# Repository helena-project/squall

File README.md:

Squall
======

Squall is a low cost, 1 inch round BLE sensor tag based on the Nordic
nRF51822 BLE / Cortex M0 SoC. It is designed to be the basis for experimenting
with BLE tag platforms.

### Squall Versions

Squall comes in two flavors: a stripped down version with only the essentials
that has a raw cost just over $5. This includes the SoC, an antenna, expansion
headers, and a battery clip. This version is targeted towards sensor deployments
where a low cost per device is essential to permit larger deployments.

The second version adds USB support so that the nRF51822 can be programmed
with a serial bootloader, and adds a reset button and 32 kHz crystal. This
design is intended to be easier to get started with as it only requires
a USB connection to program. It also supports a rechargeable battery that
will charge over USB.

### Hardware Tools

To aid developing with Squall, there is a
[breakout board](/hardware/squall-breakout/rev_b) that makes it easier to debug
signals and program the board.

To program Squall over JTAG, there is an
[adapter board](https://github.com/lab11/nrf51-tools/tree/master/hardware/jlink_to_tag/rev_b)
that adapts the J-Link JTAG 20-pin header to the much smaller
[tag connect](http://www.tag-connect.com/catalog/6) header.

Daughter Boards
---------------

Squall is designed to be a base BLE platform with shields on top. A couple
shields have been developed:

- [Rain](/hardware/rain) - Sensing platform for wearable exploration.
- [BLEES](https://github.com/lab11/blees) - Environmental sensing platform.

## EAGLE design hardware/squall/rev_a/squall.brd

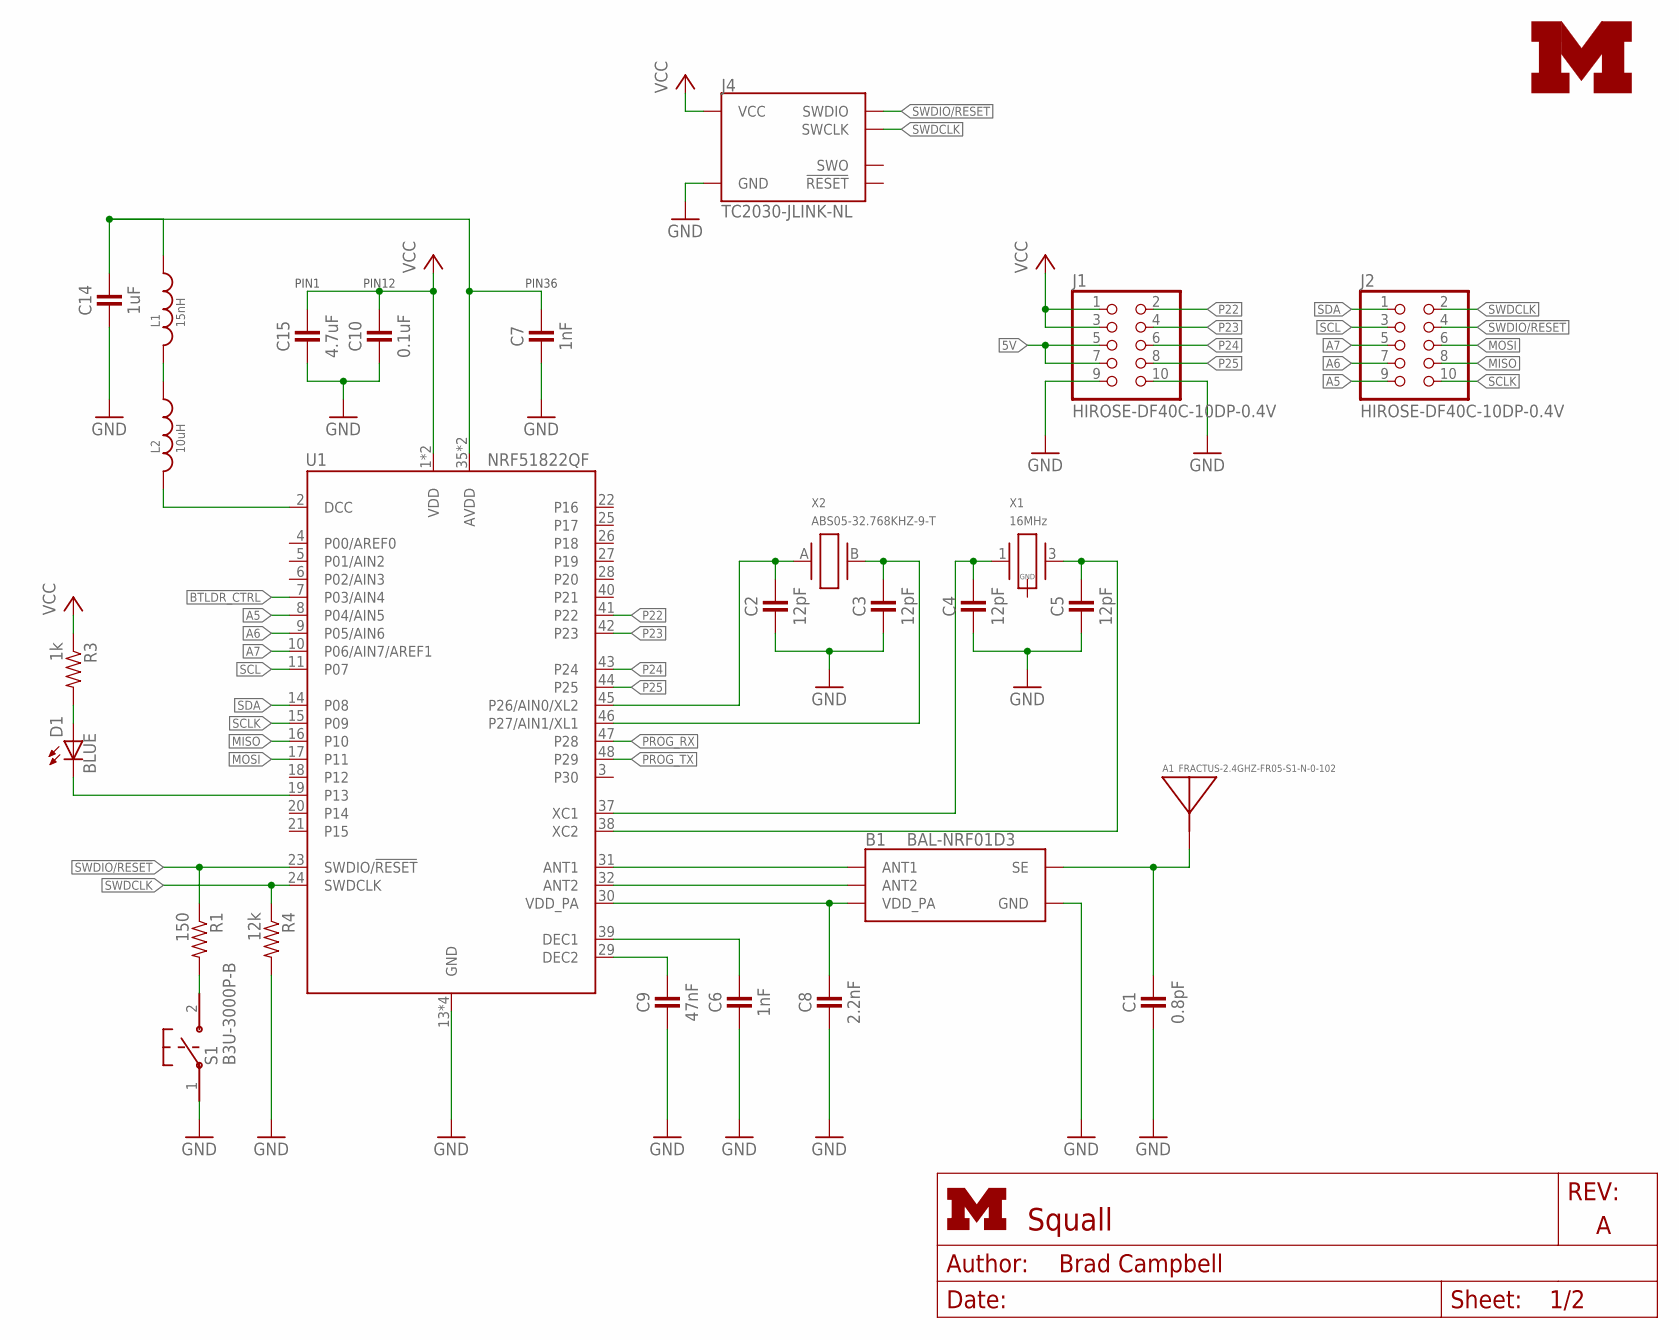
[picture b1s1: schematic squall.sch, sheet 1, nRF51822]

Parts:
A1: FRACTUS-2.4GHZ-FR05-S1-N-0-102; FRACTUS-ANTENNA-FR05-S1-N-0-102
B1: BAL-NRF01D3
C1: 0.8pF; 0402_CAP; MPN GRM1555C1HR80BA01D; DIGIKEY 490-6269-1-ND
C2, C3, C4, C5: 12pF; 0402_CAP; MPN GRM1555C1H120GA01D; DIGIKEY 490-6197-1-ND
C6, C7: 1nF; 0402_CAP; MPN GRM155R71H102KA01D; DIGIKEY 490-1303-1-ND
C8: 2.2nF; 0402_CAP; MPN GRM155R71E222KA01D; DIGIKEY 490-5419-1-ND
C9: 47nF; 0402_CAP; MPN C1005X7R1C473K050BC; DIGIKEY 445-1264-1-ND
C10: 0.1uF; 0402_CAP; MPN GRM155R61A104KA01D; DIGIKEY 490-1318-1-ND
C14: 1uF; 0402_CAP; MPN CL05B105KQ5NQNC; DIGIKEY 1276-1513-1-ND
C15: 4.7uF; 0402_CAP; MPN C1005X5R0J475K050BC; DIGIKEY 445-5947-1-ND
D1: BLUE; LED-0603
J1, J2: HIROSE-DF40C-10DP-0.4V; 2X5/SMD/0.4MM
J4: TC2030-JLINK-NL; TC2030-IDC-NL
L1: 15nH; 0402_CAP; MPN HK100515NJ-T; DIGIKEY 587-1521-1-ND
L2: 10uH; 0603_CAP; MPN LQM18FN100M00D; DIGIKEY 490-4025-1-ND
LOGO1: UMICH_SOLID_TINY; UMICH_SOLID_50MIL
R1: 150; 0402_RES; MPN MCR01MRTF1500; DIGIKEY RHM150CDCT-ND
R3: 1k; 0402_RES; MPN RC1005J102CS; DIGIKEY 1276-4376-1-ND
R4: 12k; 0402_RES; MPN RC1005F123CS; DIGIKEY 1276-4122-1-ND
S1: B3U-3000P-B
U1: NRF51822QF; QFN-48-6MM
X1: 16MHz; TXC-8Y; MPN 8Y-16.000MAAV-T; DIGIKEY 887-2003-1-ND
X2: ABS05-32.768KHZ-9-T; ABS05

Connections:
5V: J1.5, J1.7; also elsewhere on the board
A0: C2.1, U1.45 (P26/AIN0/XL2), X2.A (1)
A1: C3.1, U1.46 (P27/AIN1/XL1), X2.B (2)
A5: J2.9, U1.8 (P04/AIN5)
A6: J2.7, U1.9 (P05/AIN6)
A7: J2.5, U1.10 (P06/AIN7/AREF1)
AVDD: C7.1, C14.1, L1.1, U1.35 (AVDD), U1.36 (AVDD)
BTLDR_CTRL: U1.7 (P03/AIN4); also elsewhere on the board
DCC: L2.2, U1.2 (DCC)
GND: B1.GND, C1.2, C2.2, C3.2, C4.2, C5.2, C6.2, C7.2, C8.2, C9.2, C10.2, C14.2, C15.2, J1.9, J1.10, J4.5 (GND), R4.2, S1.1, U1.13 (GND), U1.33 (GND), U1.34 (GND), U1.GND; also elsewhere on the board
MISO: J2.8, U1.16 (P10)
MOSI: J2.6, U1.17 (P11)
unnamed: B1.ANT1, U1.31 (ANT1)
unnamed: B1.ANT2, U1.32 (ANT2)
unnamed: D1.C, U1.19 (P13)
unnamed: R1.2, S1.2
unnamed: A1.1, B1.SE, C1.1
unnamed: L1.2, L2.1
unnamed: C4.1, U1.37 (XC1), X1.1
unnamed: C5.1, U1.38 (XC2), X1.3 (2)
unnamed: C6.1, U1.39 (DEC1)
unnamed: C9.1, U1.29 (DEC2)
unnamed: D1.A, R3.2
P22: J1.2, U1.41 (P22)
P23: J1.4, U1.42 (P23)
P24: J1.6, U1.43 (P24)
P25: J1.8, U1.44 (P25)
PROG_RX: U1.47 (P28); also elsewhere on the board
PROG_TX: U1.48 (P29); also elsewhere on the board
SCL: J2.3, U1.11 (P07)
SCLK: J2.10, U1.15 (P09)
SDA: J2.1, U1.14 (P08)
SWDCLK: J2.2, J4.4 (SWCLK), R4.1, U1.24 (SWDCLK)
SWDIO/!RESET: J2.4, J4.2 (SWDIO), R1.1, U1.23 (SWDIO/!RESET)
VCC: C10.1, C15.1, J1.1, J1.3, J4.1 (VCC), R3.1, U1.1 (VDD), U1.12 (VDD); also elsewhere on the board
VDD_PA: B1.VCC (VDD_PA), C8.1, U1.30 (VDD_PA)

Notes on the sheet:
PIN1
PIN12
PIN36

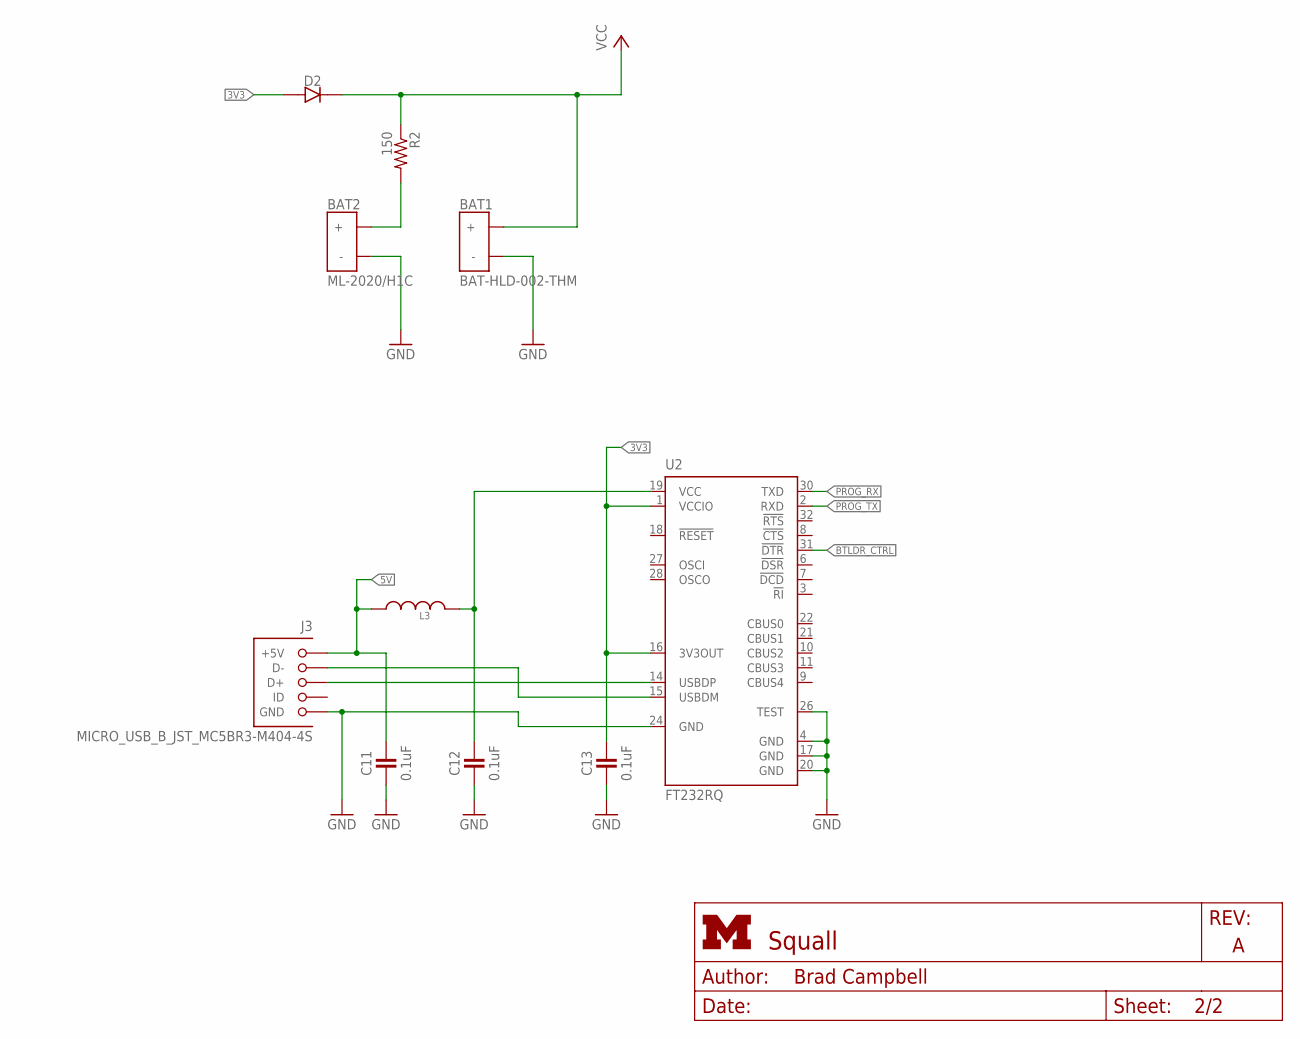
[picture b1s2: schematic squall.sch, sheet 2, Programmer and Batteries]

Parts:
BAT1: BAT-HLD-002-THM
BAT2: ML-2020/H1C
C11, C12, C13: 0.1uF; 0402_CAP; MPN GRM155R61A104KA01D; DIGIKEY 490-1318-1-ND
D2: DIODE; 0402_DIODE; MPN CDBQR0130L; DIGIKEY 641-1271-1-ND
J3: MICRO_USB_B_JST_MC5BR3-M404-4S; USB_MICRO_B-JST-MC5BR3-M404-4S-TB
L3: INDUCTOR0402; 0402_CAP; DIGIKEY 445-2979-1-ND
R2: 150; 0402_RES; MPN MCR01MRTF1500; DIGIKEY RHM150CDCT-ND
U2: FT232RQ; QFN32

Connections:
3V3: C13.1, D2.ANODE, U2.1 (VCCIO), U2.16 (3V3OUT)
5V: C11.1, J3.1 (+5V), L3.1; also elsewhere on the board
BTLDR_CTRL: U2.31 (!DTR); also elsewhere on the board
FTDI_VCC: C12.1, L3.2, U2.19 (VCC)
GND: BAT1.GND (-), BAT2.NEG (-), C11.2, C12.2, C13.2, J3.5 (GND), U2.4 (GND), U2.17 (GND), U2.20 (GND), U2.24 (GND), U2.26 (TEST); also elsewhere on the board
unnamed: BAT2.POS (+), R2.2
unnamed: J3.3 (D+), U2.14 (USBDP)
unnamed: J3.2 (D-), U2.15 (USBDM)
PROG_RX: U2.30 (TXD); also elsewhere on the board
PROG_TX: U2.2 (RXD); also elsewhere on the board
VCC: BAT1.POS1 (+), BAT1.POS2 (+), BAT1.POS3 (+), BAT1.POS4 (+), D2.CATHODE, R2.1; also elsewhere on the board

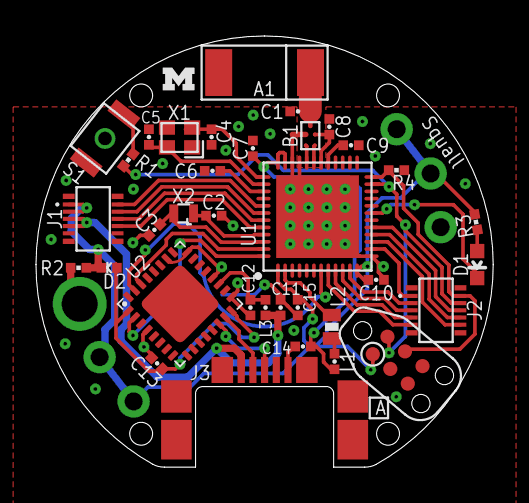
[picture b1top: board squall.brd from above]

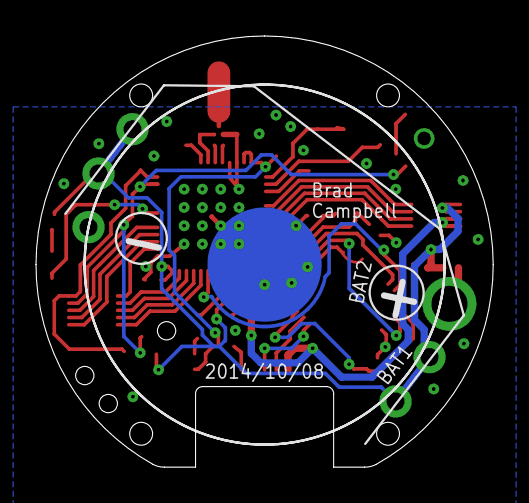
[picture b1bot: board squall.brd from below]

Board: 2 copper layers, 25.4 x 24.0 mm, 38 parts (2 on the bottom side), 41 nets.

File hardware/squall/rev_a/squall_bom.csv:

Qty,Value,Device,Package,Parts,Description,DIGIKEY,MOUSER,NEWARK,RICHARDSON_RFPD,Price Each (1000),Quantity (A),Cost (A),Quantity (B),Cost (B)
1,FRACTUS-2.4GHZ-FR05-S1-N-0-102,FRACTUS-2.4GHZ-FR05-S1-N-0-102,FRACTUS-ANTENNA-FR05-S1-N-0-102,A1,"Fractus Compact Reach XtendTM chip antenna is engineered specifically for Bluetooth,",,,,FR05-S1-N-0102B,0.74,1,0.74,1,0.74
1,BAL-NRF01D3,BAL-NRF01D3,BAL-NRF01D3,B1,"50 ohm nominal input / conjugate match balun to nRF51422-QFAA,",497-13637-1-ND,511-BAL-NRF01D3,,,0.337,1,0.337,1,0.337
1,BAT-HLD-002-THM,BAT-HLD-002-THM,BAT-HLD-002-THM,BAT1,RETAINER BATT CR2025/2032 PC PIN,BAT-HLD-001-THM-ND,,,,0.20125,1,0.20125,,0
1,ML-2020/H1C,ML-2020/H1C,ML-2020/H1C,BAT2,BATT LITH COIN 3V RECHARGE PINS 45mAh,P047-ND,658-ML-2020/H1CN,,,1.4025,,0,1,1.4025
1,0.8pF,CAPACITOR,0402_CAP,C1,0402 Capacitor,490-5419-1-ND,,,,0.0127,1,0.0127,1,0.0127
4,12pF,CAPACITOR,0402_CAP,"C2, C3, C4, C5",0402 Capacitor,490-6197-1-ND,,,,0.0178,2,0.0356,4,0.0712
2,1nF,CAPACITOR,0402_CAP,"C6, C7",0402 Capacitor,490-1303-1-ND,,,,0.01009,2,0.02018,2,0.02018
1,2.2nF,CAPACITOR,0402_CAP,C8,0402 Capacitor,490-5419-1-ND,,,,0.0127,1,0.0127,1,0.0127
1,47nF,CAPACITOR,0402_CAP,C9,0402 Capacitor,445-1264-1-ND,,,,0.0151,1,0.0151,1,0.0151
1,0.1uF,CAPACITOR,0402_CAP,C10,0402 Capacitor,445-4952-1-ND,,,,0.0136,1,0.0136,1,0.0136
3,0.1uF,CAPACITOR,0402_CAP,"C11, C12, C13",0402 Capacitor,490-1318-6-ND,,,,0.01,,0,3,0.03
1,1uF,CAPACITOR,0402_CAP,C14,0402 Capacitor,1276-1513-1-ND,,,,0.058,,0,1,0.058
1,4.7uF,CAPACITOR,0402_CAP,C15,0402 Capacitor,445-5947-1-ND,,,,0.122,,0,1,0.122
1,BLUE,LED0603,LED-0603,D1,LED 468NM BLUE CLEAR 0603 SMD,160-1647-1-ND,,,,0.0925,1,0.0925,1,0.0925
1,DIODE,DIODE,0402_DIODE,D2,DIODE SCHOTTKY 30V 0.1A 0402,641-1271-1-ND,750-CDBQR0130L,,,0.11,,0,1,0.11
2,HIROSE-DF40C-10DP-0.4V,HIROSE-DF40C-10DP-0.4V,2X5/SMD/0.4MM,"J1, J2",DF40 Series Header - 0.4MM Pitch,H11616CT-ND,798-DF40C10DP0.4V51,68X2585,,0.38815,2,0.7763,2,0.7763
1,MICRO_USB_B_JST_MC5BR3-M404-4S,MICRO_USB_B_JST_MC5BR3-M404-4S,USB_MICRO_B-JST-MC5BR3-M404-4S-TB,J3,Micro USB B mid mount,455-2567-2-ND,53X3655,,,0.60558,,0,1,0.60558
1,15nH,INDUCTOR0402,0402_CAP,L1,INDUCTOR HI FREQ 15NH 5% 0402,587-1521-1-ND,,,,0.034,1,0.034,1,0.034
1,10uH,INDUCTOR0603,0603_CAP,L2,INDUCTOR 10UH 50MA 0603,490-4025-1-ND,,,,0.07434,1,0.07434,1,0.07434
1,,INDUCTOR0402,0402_CAP,L3,FERRITE CHIP 30 OHM 1.7A 0402,445-2979-1-ND,,,,0.0334,,0,1,0.0334
2,150,RESISTOR,0402_RES,"R1, R2",Resistor,RHM150CDCT-ND,,,,0.00933,,0,2,0.01866
1,1k,RESISTOR,0402_RES,R3,Resistor,RHM1.0KCECT-ND,,,,0.00933,1,0.00933,1,0.00933
1,12k,RESISTOR,0402_RES,R4,Resistor,RHM12.0KCDCT-ND,,,,0.00933,1,0.00933,1,0.00933
1,B3U-3000P-B,B3U-3000P-B,B3U-3000P-B,S1,SWITCH TACTILE SPST-NO 0.05A 12V,SW1256CT-ND,,,,0.66414,,0,1,0.66414
1,NRF51822QF,NRF51822QF,QFN-48-6MM,U1,Multiprotocol Bluetooth® 4.0 low energy/2.4 GHz RF SoC 256K,1490-1031-1-ND,,,,2.31,1,2.31,1,2.31
1,FT232RQ,FT232RQ,QFN32,U2,IC USB FS SERIAL UART 32-QFN,768-1008-1-ND,,91K9919,,3.301,,0,1,3.301
1,16MHz,TXC-8Y,TXC-8Y,X1,CRYSTAL 16MHZ 8PF SMD,887-2003-1-ND,,,,0.782,1,0.782,1,0.782
1,ABS05-32.768KHZ-9-T,ABS05-32.768KHZ-9-T,ABS05,X2,32.768kHz Crystal,535-11897-1-ND,,,,1.061,,0,1,1.061
,,,,,BATTERY LITHIUM COIN 3V 20MM CR2032,P189-ND,,,,0.15579,1,0.15579,,
,,,,,,,,,,,,5.63172,,12.71656

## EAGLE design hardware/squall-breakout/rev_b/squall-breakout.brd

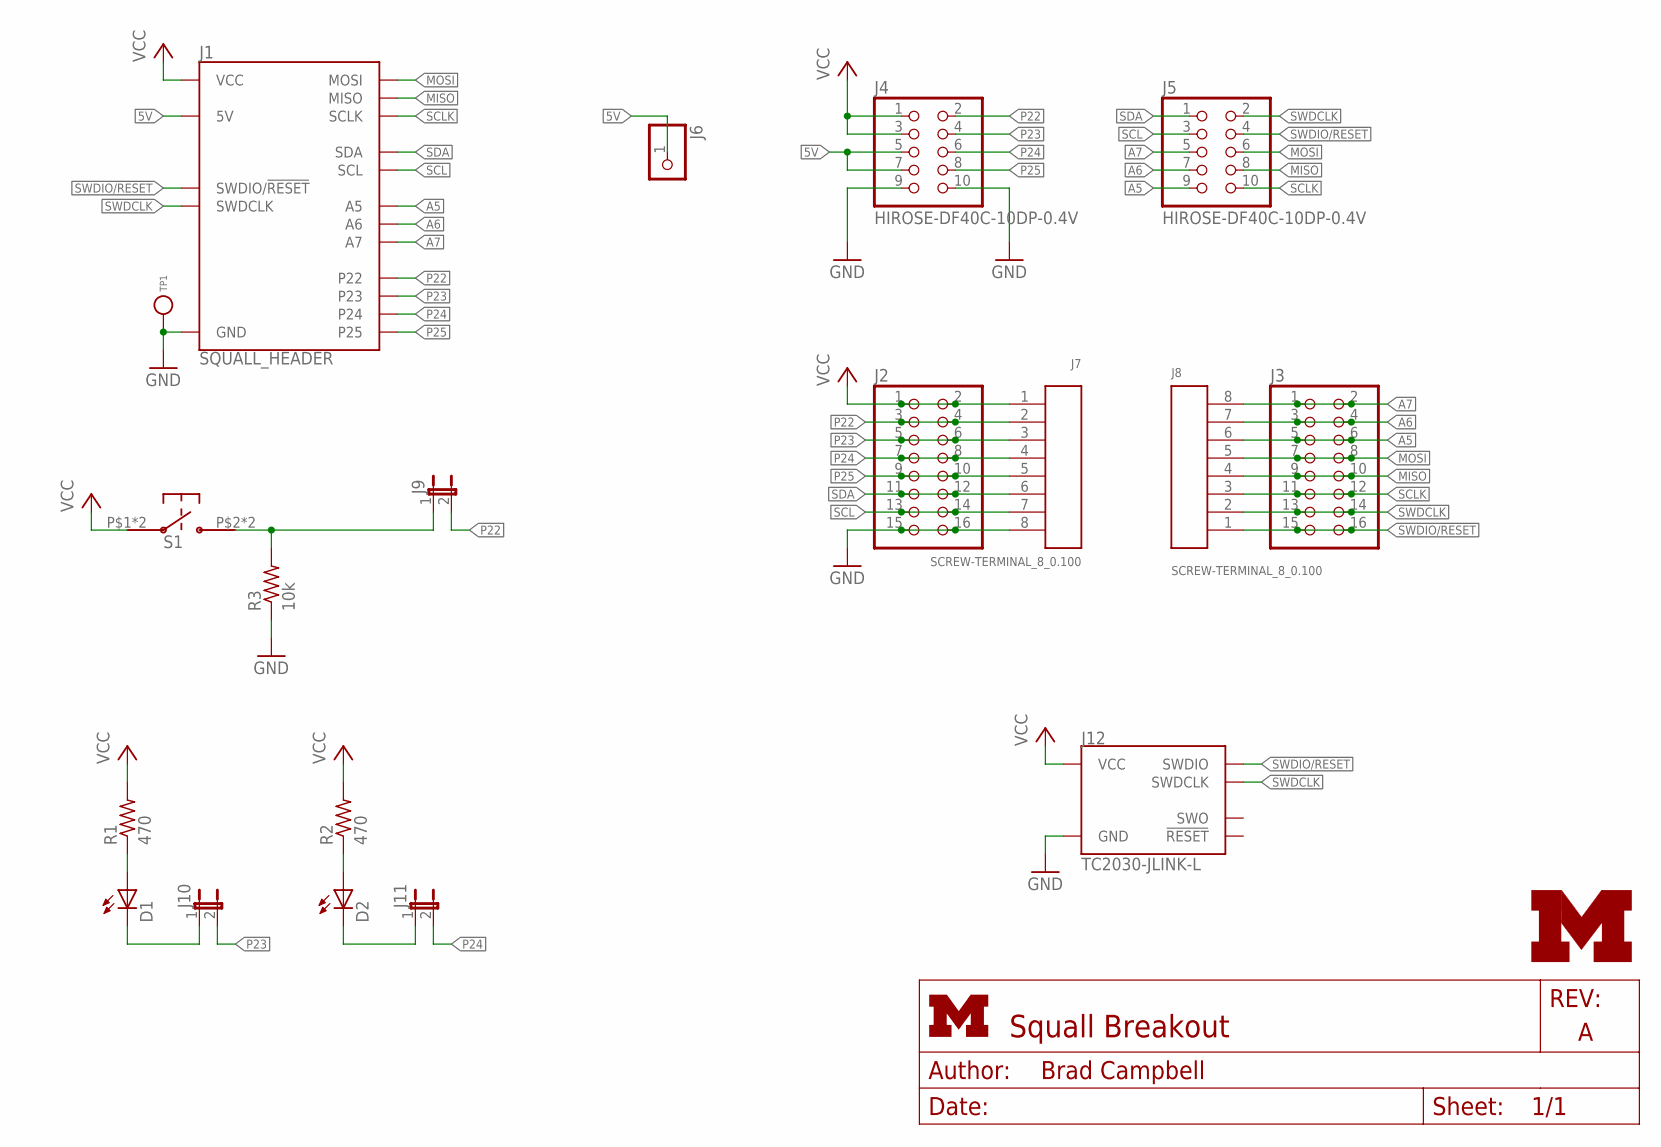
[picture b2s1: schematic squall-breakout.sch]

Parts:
D1, D2: LED0603; LED-0603
J1: SQUALL_HEADER
J2, J3: PINHD-2X8; 2X08
J4, J5: HIROSE-DF40C-10DP-0.4V; 2X5/SMD/0.4MM
J6: PINHD-1X1; 1X01
J7, J8: SCREW-TERMINAL_8_0.100; CONN_BLOCK_8
J9, J10, J11: JUMPER-2PTH; 1X02
J12: TC2030-JLINK-L; TC2030-IDC
LOGO1: UMICH_SOLID_TINY; UMICH_SOLID_50MIL
R1, R2: 470; R0603
R3: 10k; R0603
S1: EVQP2
TP1: TEST_POINT_0.112IN; TESTPOINT_0.112IN

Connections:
5V: J1.A5 (5V), J1.A7 (5V), J4.5, J4.7, J6.1
A5: J1.B9 (A5), J3.5, J3.6, J5.9, J8.6
A6: J1.B7 (A6), J3.3, J3.4, J5.7, J8.7
A7: J1.B5 (A7), J3.1, J3.2, J5.5, J8.8
GND: J1.A9 (GND), J1.A10 (GND), J2.15, J2.16, J4.9, J4.10, J7.8, J12.5 (GND), R3.1, TP1.1
MISO: J1.B8 (MISO), J3.9, J3.10, J5.8, J8.4
MOSI: J1.B6 (MOSI), J3.7, J3.8, J5.6, J8.5
unnamed: J9.1, R3.2, S1.P$2, S1.P$4
unnamed: D1.A, R1.1
unnamed: D1.C, J10.1
unnamed: D2.A, R2.1
unnamed: D2.C, J11.1
P22: J1.A2 (P22), J2.3, J2.4, J4.2, J7.2, J9.2
P23: J1.A4 (P23), J2.5, J2.6, J4.4, J7.3, J10.2
P24: J1.A6 (P24), J2.7, J2.8, J4.6, J7.4, J11.2
P25: J1.A8 (P25), J2.9, J2.10, J4.8, J7.5
SCL: J1.B3 (SCL), J2.13, J2.14, J5.3, J7.7
SCLK: J1.B10 (SCLK), J3.11, J3.12, J5.10, J8.3
SDA: J1.B1 (SDA), J2.11, J2.12, J5.1, J7.6
SWDCLK: J1.B2 (SWDCLK), J3.13, J3.14, J5.2, J8.2, J12.4 (SWDCLK)
SWDIO/!RESET: J1.B4 (SWDIO/!RESET), J3.15, J3.16, J5.4, J8.1, J12.2 (SWDIO)
VCC: J1.A1 (VCC), J1.A3 (VCC), J2.1, J2.2, J4.1, J4.3, J7.1, J12.1 (VCC), R1.2, R2.2, S1.P$1, S1.P$3

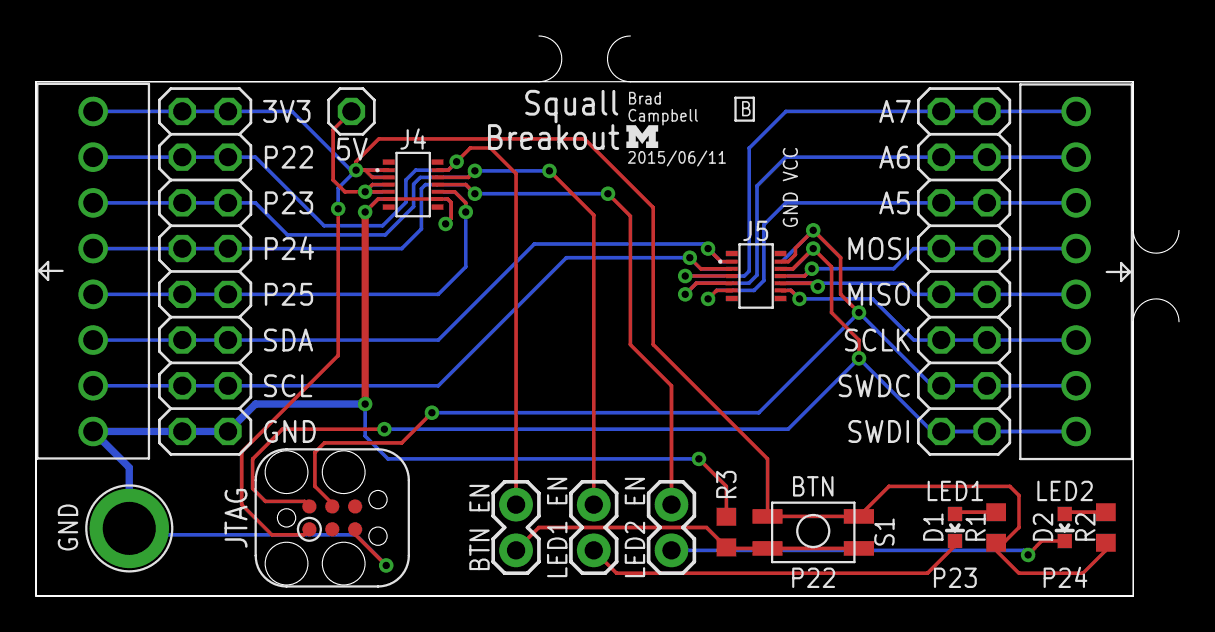
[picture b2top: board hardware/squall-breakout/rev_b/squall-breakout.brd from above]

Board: 2 copper layers, 63.5 x 31.1 mm, 20 parts (0 on the bottom side), 22 nets.

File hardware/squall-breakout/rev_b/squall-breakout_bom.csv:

# Bill of Materials
# Converted from squall-breakout_bom.xlsx
# Generated by bom_to_text.py

Qty,Value,Device,Package,Parts,Description,DIGIKEY,MOUSER,NEWARK
2,,LED0603,LED-0603,"D1, D2",LEDs,,,
2,SQUALL_HEADER,SQUALL_HEADER,SQUALL_HEADER,J1,Header for a sensor board on top of the Squall BLE tag board.,H11617CT-ND,,
2,,PINHD-2X8,2X08,"J2, J3",PIN HEADER,609-3364-ND,649-68602-116HLF,20M2833
2,HIROSE-DF40C-10DP-0.4V,HIROSE-DF40C-10DP-0.4V,2X5/SMD/0.4MM,"J4, J5",DF40 Series Header - 0.4MM Pitch,H11616CT-ND,798-DF40C10DP0.4V51,68X2585
1,,PINHD-1X1,1X01,J6,PIN HEADER,A107006-ND,,
2,SCREW-TERMINAL_8_0.100,SCREW-TERMINAL_8_0.100,CONN_BLOCK_8,"J7, J8",8x 0.100 in screw terminal block,277-1279-ND,651-1725711,71C4111
3,,JUMPER-2PTH,1X02,"J9, J10, J11",Jumper,3M9447-ND,,
2,470,R-US_R0603,R0603,"R1, R2","RESISTOR, American symbol",,,
1,10k,R-US_R0603,R0603,R3,"RESISTOR, American symbol",,,
1,EVQP2,EVQP2,EVQP2,S1,SWITCH TACTILE SPST-NO 0.02A 15V,P11084SCT-ND,,
1,TEST_POINT_0.112IN,TEST_POINT_0.112IN,TESTPOINT_0.112IN,TP1,"Solder terminal, turreted",,,40F6015

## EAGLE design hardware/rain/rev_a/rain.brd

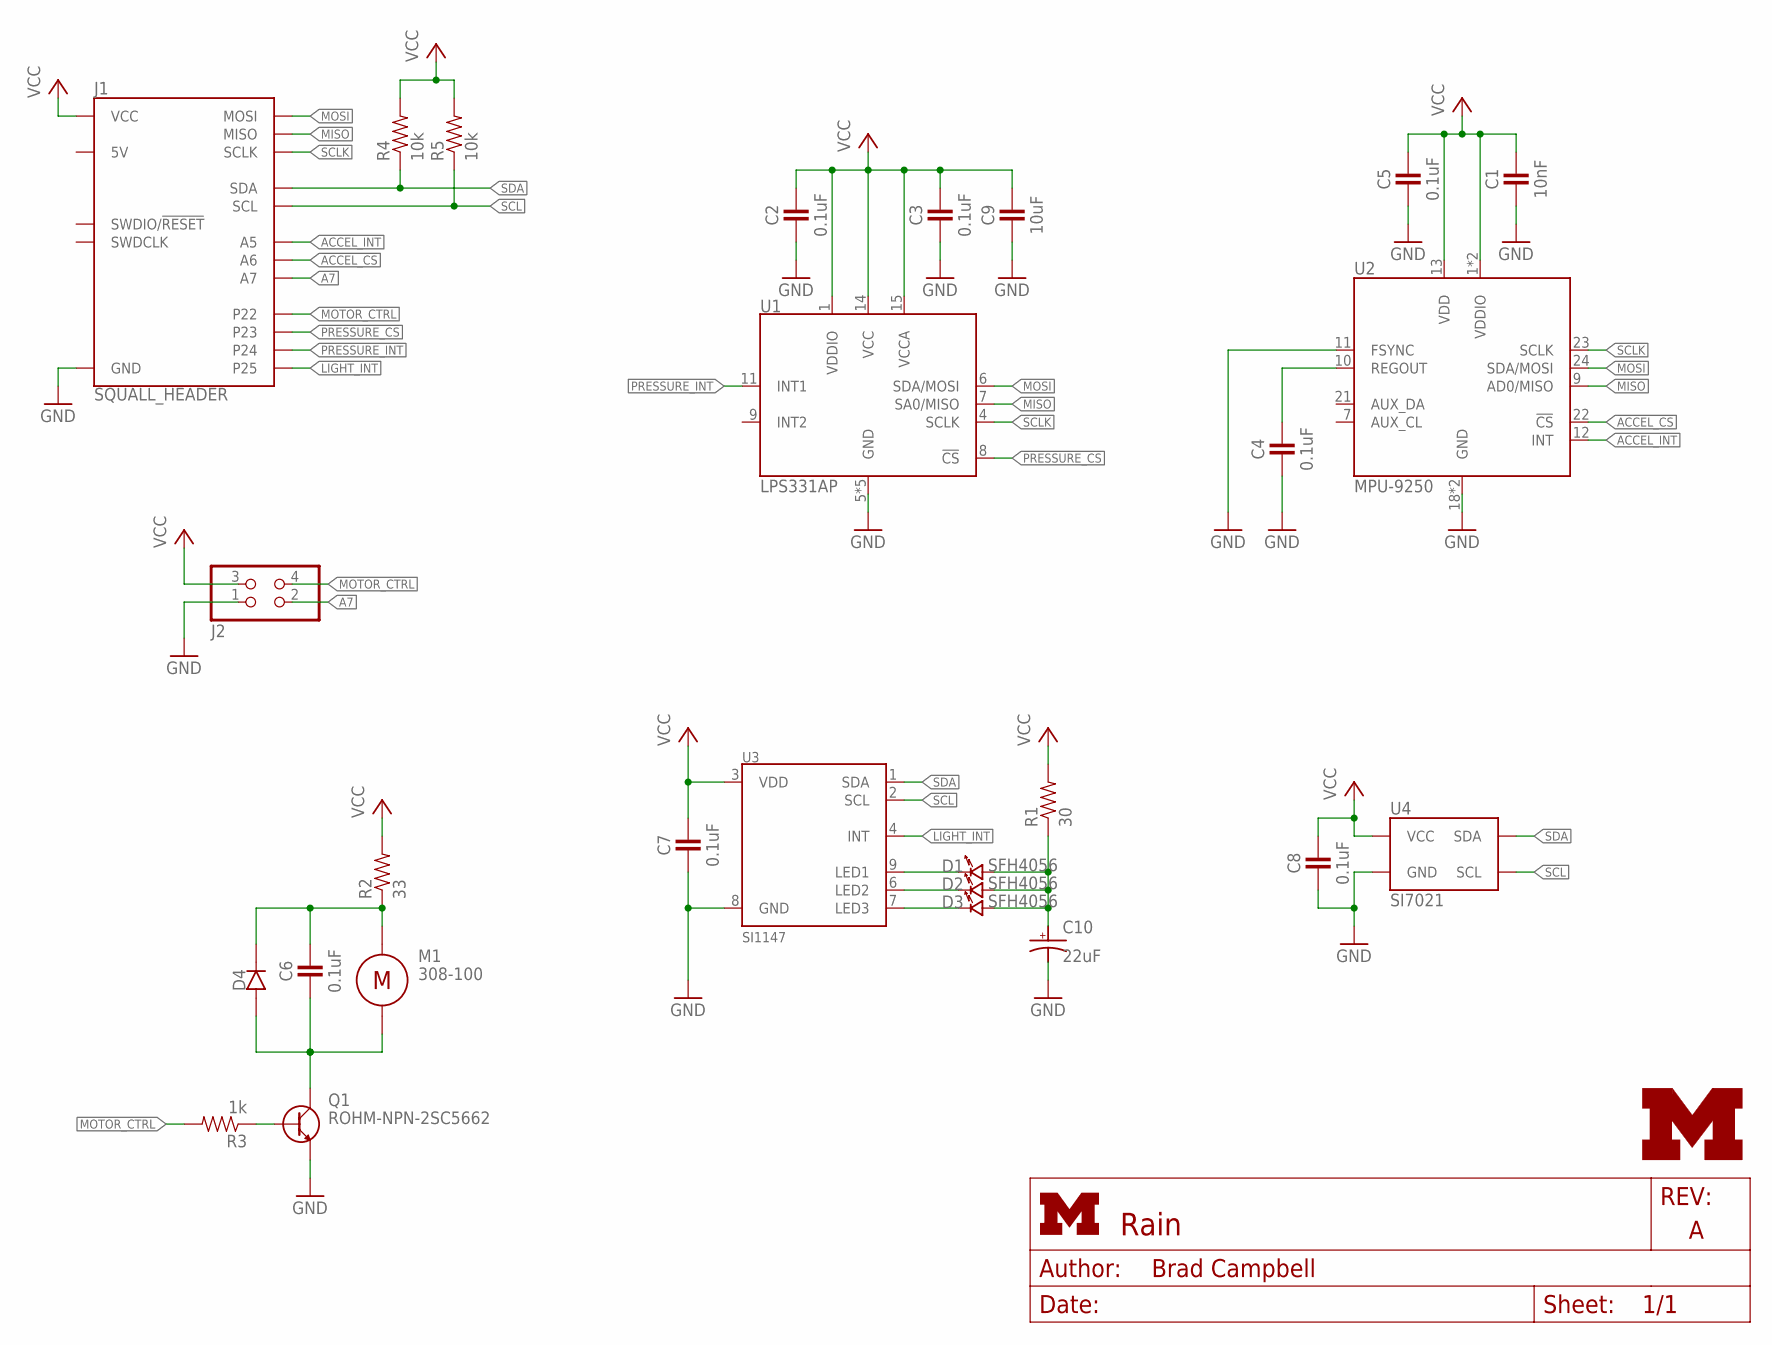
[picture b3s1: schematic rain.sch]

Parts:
C1: 10nF; 0402_CAP; DIGIKEY 490-1312-1-ND
C2, C3, C4, C5, C6, C7, C8: 0.1uF; 0402_CAP; DIGIKEY 490-1318-1-ND
C9: 10uF; 0402_CAP; DIGIKEY 445-8919-1-ND
C10: 22uF; CAP0603; DIGIKEY 511-1493-1-ND
D1, D2, D3: SFH4056
D4: DIODE; 0402_DIODE; DIGIKEY 641-1277-1-nd
J1: SQUALL_HEADER
J2: PINHD-2X2; 2X02; DIGIKEY 609-3201-ND
LOGO1: UMICH_SOLID_TINY; UMICH_SOLID_50MIL
M1: 308-100
Q1: ROHM-NPN-2SC5662; VMT3
R1: 30; 0402_RES; DIGIKEY RHM30CECT-ND
R2: 33; 0402_RES; DIGIKEY RHM33CECT-ND
R3: 1k; 0402_RES; DIGIKEY RHM1.0KCECT-ND
R4, R5: 10k; 0402_RES; DIGIKEY RHM10.0KCDCT-ND
U1: LPS331AP; HCLGA-16/3MM
U2: MPU-9250; QFN-24/3MM
U3: SI1147; QFN-10/2MM
U4: SI7021; DFN-6/3MM

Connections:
!ACCEL_CS: J1.B7 (A6), U2.22 (!CS)
!PRESSURE_CS: J1.A4 (P23), U1.8 (!CS)
A7: J1.B5 (A7), J2.2
ACCEL_INT: J1.B9 (A5), U2.12 (INT)
GND: C1.2, C2.2, C3.2, C4.2, C5.2, C7.2, C8.2, C9.2, C10.NEG (ANODE), J1.A9 (GND), J1.A10 (GND), J2.1, Q1.2 (EMITTER), U1.5 (GND), U1.10 (GND), U1.12 (GND), U1.13 (GND), U1.16 (GND), U2.11 (FSYNC), U2.18 (GND), U2.20 (GND), U3.8 (GND), U4.2 (GND)
LIGHT_INT: J1.A8 (P25), U3.4 (INT)
MISO: J1.B8 (MISO), U1.7 (SA0/MISO), U2.9 (AD0/MISO)
MOSI: J1.B6 (MOSI), U1.6 (SDA/MOSI), U2.24 (SDA/MOSI)
MOTOR_CTRL: J1.A2 (P22), J2.4, R3.2
unnamed: C6.1, D4.CATHODE, M1.POS, R2.1
unnamed: C6.2, D4.ANODE, M1.NEG, Q1.3 (COLLECTOR)
unnamed: C4.1, U2.10 (REGOUT)
unnamed: D1.CATHODE, U3.9 (LED1)
unnamed: Q1.1 (BASE), R3.1
unnamed: D2.CATHODE, U3.6 (LED2)
unnamed: D3.CATHODE, U3.7 (LED3)
unnamed: C10.POS (CATHODE), D1.ANODE, D2.ANODE, D3.ANODE, R1.1
PRESSURE_INT: J1.A6 (P24), U1.11 (INT1)
SCL: J1.B3 (SCL), R5.1, U3.2 (SCL), U4.6 (SCL)
SCLK: J1.B10 (SCLK), U1.4 (SCLK), U2.23 (SCLK)
SDA: J1.B1 (SDA), R4.1, U3.1 (SDA), U4.1 (SDA)
VCC: C1.1, C2.1, C3.1, C5.1, C7.1, C8.1, C9.1, J1.A1 (VCC), J1.A3 (VCC), J2.3, R1.2, R2.2, R4.2, R5.2, U1.1 (VDDIO), U1.14 (VCC), U1.15 (VCCA), U2.1 (VDDIO), U2.8 (VDDIO), U2.13 (VDD), U3.3 (VDD), U4.5 (VCC)

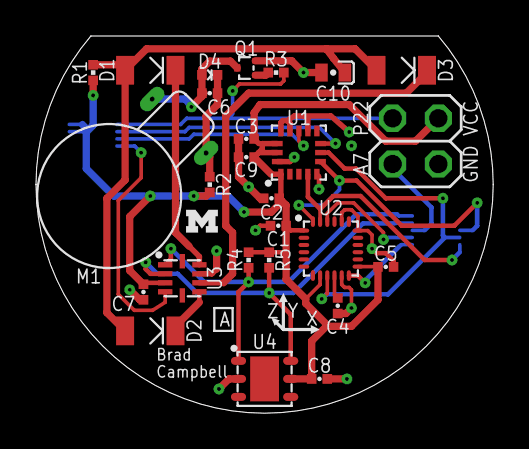
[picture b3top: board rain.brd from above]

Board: 2 copper layers, 25.4 x 21.0 mm, 28 parts (0 on the bottom side), 22 nets.

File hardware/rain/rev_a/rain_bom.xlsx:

Qty | Value | Device | Package | Parts | Description | DIGIKEY | PRECISION_MICRODRIVES
1 | 10nF | CAPACITOR | 0402_CAP | C1 | 0402 Capacitor | 490-1312-1-ND
7 | 0.1uF | CAPACITOR | 0402_CAP | C2, C3, C4, C5, C6, C7, C8 | 0402 Capacitor | 490-1318-1-ND
1 | 10uF | CAPACITOR | 0402_CAP | C9 | 0402 Capacitor | 445-8919-1-ND
1 | 22uF | CAP_POL0603 | CAP0603 | C10 | 0603 Tantalum Capacitor | 511-1493-1-ND
3 | SFH4056 | SFH4056 | SFH4056 | D1, D2, D3 | LED IR EMITTER 850NM | 475-3042-1-ND
1 | DIODE | DIODE | 0402_DIODE | D4 |  | 641-1277-1-ND
2 | SQUALL_HEADER | SQUALL_HEADER | SQUALL_HEADER | J1 | Header for a sensor board on top of the Squall BLE tag board. | H11617CT-ND
1 |  | PINHD-2X2 | 2X02 | J2 | PIN HEADER | 609-3201-ND
1 | 308-100 | 308-100 | 308-100 | M1 | Pico Vibe |  | 308-100
1 | ROHM-NPN-2SC5662 | ROHM-NPN-2SC5662 | VMT3 | Q1 |  | 2SC5662T2LPCT-ND
1 | 30 | RESISTOR0402_RES | 0402_RES | R1 | Resistor | RHM30CECT-ND
1 | 33 | RESISTOR0402_RES | 0402_RES | R2 | Resistor | RHM33CECT-ND
1 | 1k | RESISTOR0402_RES | 0402_RES | R3 | Resistor | RHM1.0KCECT-ND
2 | 10k | RESISTOR0402_RES | 0402_RES | R4, R5 | Resistor | RHM10.0KCDCT-ND
1 | LPS331AP | LPS331AP | HCLGA-16/3MM | U1 | IC PRESSURE SENSOR PIEZO 16HCLGA | 497-12927-1-ND
1 | MPU-9250 | MPU-9250 | QFN-24/3MM | U2 | GYRO/ACCEL/COMPASS/9-AXIS | 1428-1019-1-ND
1 | SI1147 | SI1147 | QFN-10/2MM | U3 | SENSOR DGTL UV INDEX 10QFN | 336-2624-1-ND
1 | SI7021 | SI7021 | DFN-6/3MM | U4 | IC TEMP SENSOR RH 2% DFN | 336-2542-1-ND

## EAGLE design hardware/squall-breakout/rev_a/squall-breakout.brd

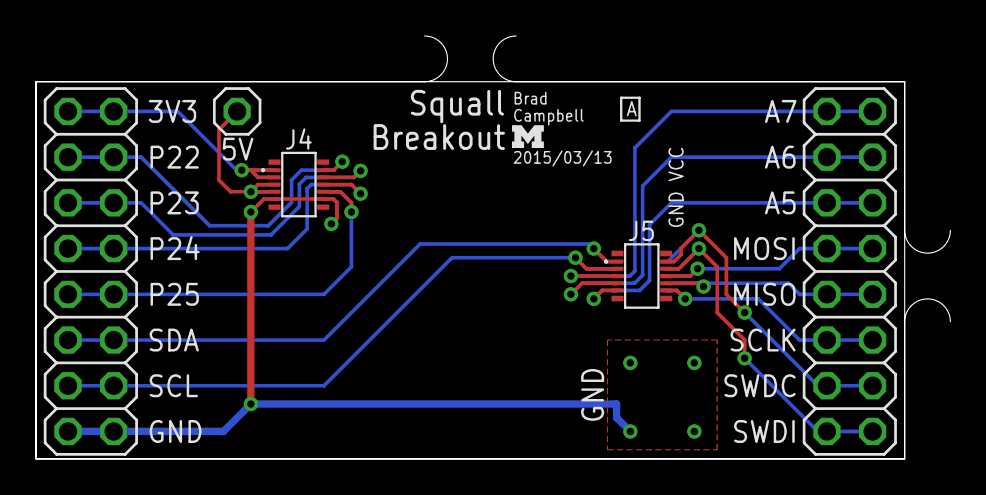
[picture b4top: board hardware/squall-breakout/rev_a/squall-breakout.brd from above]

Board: 2 copper layers, 50.8 x 23.5 mm, 7 parts (0 on the bottom side), 17 nets.

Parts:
J1: SQUALL_HEADER
J2, J3: 2X08
J4, J5: HIROSE-DF40C-10DP-0.4V; 2X5/SMD/0.4MM
J6: 1X01
LOGO1: UMICH_SOLID_TINY; UMICH_SOLID_50MIL

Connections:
5V: J1.A5, J1.A7, J4.5, J4.7, J6.1
A5: J1.B9, J3.5, J3.6, J5.9
A6: J1.B7, J3.3, J3.4, J5.7
A7: J1.B5, J3.1, J3.2, J5.5
GND: J1.A9, J1.A10, J2.15, J2.16, J4.9, J4.10
MISO: J1.B8, J3.9, J3.10, J5.8
MOSI: J1.B6, J3.7, J3.8, J5.6
P22: J1.A2, J2.3, J2.4, J4.2
P23: J1.A4, J2.5, J2.6, J4.4
P24: J1.A6, J2.7, J2.8, J4.6
P25: J1.A8, J2.9, J2.10, J4.8
SCL: J1.B3, J2.13, J2.14, J5.3
SCLK: J1.B10, J3.11, J3.12, J5.10
SDA: J1.B1, J2.11, J2.12, J5.1
SWDCLK: J1.B2, J3.13, J3.14, J5.2
SWDIO/!RESET: J1.B4, J3.15, J3.16, J5.4
VCC: J1.A1, J1.A3, J2.1, J2.2, J4.1, J4.3

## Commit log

2014-10-02 added squall
2014-10-02 started on rain
    rain is a temporary name
    sensor board for squall. better demo and data that way. also, there are
    some really cool sensors out now. thank you smart phones
2014-10-03 rain getting close
2014-10-03 rain pretty much done
    needs a name
2014-10-04 added blink software
2014-10-04 updated a digikey part num
2014-10-05 event wait
2014-10-05 add software gitignore
2014-10-05 beacon app working
2014-10-05 no adv timeout
2014-10-06 fixes: battery location and ftdi
    - rotated battery clip to hopefully not conflict with mounting holes
    - connected test on FTDI to gnd
2014-10-06 added serial bootloader app
    this gets flashed separately
2014-10-06 squall.h updated for bootloader
2014-10-06 adding files that must be changed
    some files in the sdk must be updated to support the gcc and the larger
    bootloader size
2014-10-07 bootloader seems to work with default sdk
2014-10-08 bootloader actually works now
2014-10-08 updated blink
2014-10-08 updated gitignore
2014-10-08 squall updated
2014-10-14 updated beacon app, fixed led
2014-10-14 updated beacon to work cross platform
2014-10-15 update blink app
2014-10-15 add readme for compiling and installing apps
2014-10-15 add case designs
2014-10-16 added simple sniffer app
    it blinks led when adv packet comes in
2014-10-17 added more nrf51822 hardware platforms
2014-10-17 wrote some quick code to dump adv packets
    uses spi
2014-10-17 updated gitignore`
2014-10-21 cleaned up the nrf51822 app for gateway
2014-10-23 send more data
2014-11-03 squall ids in payloads
2014-11-03 makefile update
2014-11-22 saved to noah
2015-01-14 added app for hue change application
2015-01-18 Changes to BLE beacon code from workshop
2015-02-12 commit for demo
2015-02-13 changes for demo
2015-02-13 antenna quote
2015-02-20 add firestorm
2015-02-22 added pure gcc makefile as submod
2015-02-22 updated pure gcc
2015-03-06 Remove conflict from file
2015-03-07 Added UART BLE App
    Connected to by a phone running nRF UART app
    Echos back data transmitted from phone
2015-03-07 Added a readable characteristic that updates
    Value in buffer can be updated whenever
    Buffer is 500 bytes (seems to be the maximum), but is likely packetized
    when transferred between squall and computer
2015-03-07 Commented out bug in init
2015-03-07 Accidentally deleted a line. Read works now
2015-03-12 Created basic powerblade app
    Gets data on UART and pushes to BLE advertisement
2015-03-12 squall breakout
2015-03-17 updated squall breakout
2015-03-18 Accepts only one powerblade packet at a time
2015-03-18 Testing data
2015-03-20 Advertisements start once UART data is received
2015-03-20 Changed beacon rate to 20ms
2015-03-20 Turn off UART after message received
    This should save power when advertising
2015-03-22 Added GPIO for UART and Connections
2015-03-22 Log number of connections
2015-03-25 Added two extra bytes to data payload
2015-06-04 added device informations service application
2015-06-05 fix issue where breakout pour didn't show up
2015-06-05 add custom service example
2015-06-11 add new version of squall breakout
2015-06-11 update readmes
2015-06-13 added torch
2015-06-13 torch updates
2015-06-18 Fixed MAC_ADDR for squall
2015-06-18 Added Application SRCS
2015-06-18 Added twi_hw_master.c and led.c to APPLICATION_SRCS
2015-06-25 Adding a new directory: ble_ess
2015-06-25 Updated UUIDS and made generic add char function
2015-06-26 Added Pressure
2015-06-26 Added *humidity
2015-06-26 Made it conform to the spec more. Note that humidity value is not working.
2015-06-26 Made it conform to spec more but humidity value doesn't work now
2015-06-26 Made it conform to spec more but humidity value doesn't work
2015-06-30 added ess_char_add
2015-06-30 Added some UUIDs
2015-07-02 Tried to implement triggers/noficiations
2015-07-02 Tried to update notification/ trigger
2015-07-02 Tried to update notification/trigger
2015-07-02 Trigger Setting Descriptor added, trying to make notifications work
2015-07-02 Trigger setting descriptor added, trying to get notification to work
2015-07-02 Trigger setting descriptor added, trying to get notifications working
2015-07-09 Notify works, update works, working on trigger settings. Note: humidity still doesn't work.
2015-07-10 Trying to detect trigger conditions
2015-07-14 Notifications half working (for non-time parameters)
2015-07-14 Added git ignore
2015-07-16 Trying to get bonding to work
2015-07-16 Bonding works
2015-07-17 Trying to get timers to work
2015-07-21 Timers working, app almost completely working
2015-07-22 All Triggers working for Temperature and Pressure. Humidity still a mystery...
2015-08-04 added UI download service app and a sample UI
2015-08-10 UART enable/disable on timer
2015-08-16 PowerBlade no longer times out
2015-10-09 Updated nrf51-pure-gcc-setup
2015-10-10 Updated powerblade app to send eddystone advs
    Address points to app under development by Noah
2015-10-23 change to new submodule
2015-10-23 update submodules
2015-10-23 beacon app working with new infrastructure
2015-10-23 environmental app moved to blees repo
2015-10-23 updated blink app
2015-10-23 update custom service example app
2015-10-23 update info service app to new api
2015-10-23 don't need mycolor app anymore
    just eddystone at this point
2015-10-23 updated sniffer app
2015-10-23 updated base
2015-10-23 uart app merged into powerblade
    look at powerblade for uart example
2015-10-24 moved gap app to gap repo
2015-10-24 remove old steps from readme
2015-10-24 better md formatting
2015-10-24 add not about segger serial
2015-10-24 add beacon readme
2015-10-24 add blink readme
2015-10-24 readme for sniffer
2015-10-24 Updated nrf5x-base
2015-10-27 PowerBlade app that adds ID
2015-11-19 update squall beacon to new make
2016-01-14 Updated to new simple_ble service API
2016-01-14 Updated to use simple_ble makefiles
2016-03-11 add panel zips
2016-06-09 added a mirrored squall base part
2017-09-29 squall: eagle version bump (no changes)
    There are no changes in this commit, but the newer Eagle simply
    writes the file out slightly differently, so this commit serves
    to mark those changes separately.
2017-09-29 squall: give all 0.1uF caps the same digikey attr
2017-09-29 squall: 0.1uF digikey TR -> CT to make scripts happy
2017-09-30 squall: replace obsoleted 1k resistor
2017-09-30 squall: replace obsoleted 12K resistor
2017-09-30 squall: run ERC/DRC on new eagle and resolve warnings
2017-09-30 squall: update attributes for all parts
2017-09-30 squall: updated BOM with non-obsoleted passives
    Add a readme to explain what's going on here as well.
2017-09-30 squall: add ConfigurationB 2017 assembly files
2017-09-30 remove extraneous files from archive

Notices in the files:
parts and their libraries:
SparkFun-Passives: Licensing: CC v3.0 Share-Alike You are welcome to use this library for commercial purposes.
